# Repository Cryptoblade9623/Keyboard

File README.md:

# Keyboard
A custom keyboard with a white sakura theme and a rotary encoder.
I'm making this keyboard to have an upgrade from my dying membrane keyboard that also have a lot of the keycaps missing.
I also hope that this will give me some more experience in designing PCBs and 3D models.
Because it is quite a large keyboard that I will be 3D - printing in different parts, I found some metal rods to hold them together and provide some structural support.

Instructions

1.Solder all the diodes on to the PCB

2.Place all the Mill-Max hotswap sockets into their holes

3.Stick heat resistant tape over them in top rows to keep them in place while soldering

4.Solder all the hotswap sockets

5.Solder the pin headers

6.Solder the ESP32 onto the pin headers

7.Solder the Ec11x rotary encoder on to the PCB

8.Flash the ESP32 with the firmware

9.Screw in the PCB-mount stabilizers

10.Solder 4 wires onto the 4 pads of the USBC breakout board

11.Solder 2 small capacitors and 1 big capacitor in parallel on the 5V and GND wires

12.Place heat shrink tubing to cover the solder joints on the wires 

13.Superglue the USBC board into its slot inside the Left-Base part

14.Cut the all the metal rods to 50mm

15.Join the Base pieces together with the metal rods in their slots

16.Join all the Border pieces together again using the metal rods

17.Superglue all the mountain, sakura, grass and tree pieces onto the Scenery Border piece

18.Superglue both halves of the plate together

19.Press the heat set inserts into the Border piece with a soldering iron.

20.Slot the loose wires of the USBC board though the vertical slot hole in the PCB

21.Solder the USBC wires to the D+, D-, GND and RAW of the MCU

22.Stack the parts in the order: base, PCB, plate, border and screw them all together using the M3 bolts

23.Push in the switches

24.Push in all the keycaps onto their assigned switches

25.Snap both pieces of the knob together and push the combined knob onto the rotary encoder stem

And you're done!

| Name | Purpose | Price (USD) | Seller | Link |

| :--- | :--- | :--- | :--- |

| Screws & Standoffs | Spacing, mounting, and securing internal circuit boards | $2.23 | AliExpress |[Link](https://www.aliexpress.com/item/1005008314123679.html?spm=a2g0o.cart.0.0.16e738daMmvBdI&mp=1&pdp_npi=6%40dis%21USD%21USD%202.23%21USD%202.17%21%21USD%202.17%21%21%21%402103828617851600233073312e0d3f%2112000044581940836%21ct%21GB%21-1%21%211%210%21&pdp_ext_f=%7B%22cart2PdpParams%22%3A%7B%22pdpBusinessMode%22%3A%22retail%22%7D%7D)|

| 100nF Capacitors | Providing smooth current flow to the MCU | $2.27 | AliExpress |[Link](https://www.aliexpress.com/item/1005008314123679.html?spm=a2g0o.cart.0.0.16e738daMmvBdI&mp=1&pdp_npi=6%40dis%21USD%21USD%202.23%21USD%202.17%21%21USD%202.17%21%21%21%402103828617851600233073312e0d3f%2112000044581940836%21ct%21GB%21-1%21%211%210%21&pdp_ext_f=%7B%22cart2PdpParams%22%3A%7B%22pdpBusinessMode%22%3A%22retail%22%7D%7D)|

| PCB Stabilizers | Stabilizing large mechanical keyboard keys (e.g., Spacebar, Shift) | $10.58 | AliExpress |[Link](https://www.aliexpress.com/item/4001143514438.html?spm=a2g0o.cart.0.0.16e738daMmvBdI&mp=1&pdp_npi=6%40dis%21USD%21USD%2010.58%21USD%209.80%21%21USD%209.80%21%21%21%402103828617851600233073312e0d3f%2112000033301894110%21ct%21GB%21-1%21%211%210%21)|

| Keycaps | Providing durable, custom keycaps for mechanical keyboards | $7.74 | AliExpress |[Link](https://www.aliexpress.com/item/4001143514438.html?spm=a2g0o.cart.0.0.16e738daMmvBdI&mp=1&pdp_npi=6%40dis%21USD%21USD%2010.58%21USD%209.80%21%21USD%209.80%21%21%21%402103828617851600233073312e0d3f%2112000033301894110%21ct%21GB%21-1%21%211%210%21)|

| Mechanical Switches | Actuating keystrokes quietly and smoothly in hot-swap keyboards | $19.67 | AliExpress |[Link](https://www.aliexpress.com/item/1005012344423067.html?spm=a2g0o.cart.0.0.16e738daMmvBdI&mp=1&pdp_npi=6%40dis%21USD%21USD%2019.67%21USD%2018.50%21%21USD%2018.50%21%21%21%402103828617851600233073312e0d3f%2112000058131373053%21ct%21GB%21-1%21%211%210%21)|

| Rotary Encoder | Providing rotary control and navigation inputs | $2.75 | AliExpress |[Link](https://www.aliexpress.com/item/1005012344423067.html?spm=a2g0o.cart.0.0.16e738daMmvBdI&mp=1&pdp_npi=6%40dis%21USD%21USD%2019.67%21USD%2018.50%21%21USD%2018.50%21%21%21%402103828617851600233073312e0d3f%2112000058131373053%21ct%21GB%21-1%21%211%210%21)|

| Development Board | Processing core logic, Wi-Fi, and Bluetooth functions | $7.10 | AliExpress |[Link](https://www.aliexpress.com/item/1005007319706057.html?spm=a2g0o.cart.0.0.16e738daMmvBdI&mp=1&pdp_npi=6%40dis%21USD%21USD%207.10%21USD%206.69%21%21USD%206.69%21%21%21%402103828617851600233073312e0d3f%2112000058208354042%21ct%21GB%21-1%21%211%210%21&pdp_ext_f=%7B%22cart2PdpParams%22%3A%7B%22pdpBusinessMode%22%3A%22retail%22%7D%7D)|

| Hot-swap PCB Sockets | Enabling easy and simple mechanical switch replacement on a custom PCB | $14.77 | AliExpress |[Link](https://www.aliexpress.com/item/1005007319706057.html?spm=a2g0o.cart.0.0.16e738daMmvBdI&mp=1&pdp_npi=6%40dis%21USD%21USD%207.10%21USD%206.69%21%21USD%206.69%21%21%21%402103828617851600233073312e0d3f%2112000058208354042%21ct%21GB%21-1%21%211%210%21&pdp_ext_f=%7B%22cart2PdpParams%22%3A%7B%22pdpBusinessMode%22%3A%22retail%22%7D%7D)|

| USB Type-C Connector | Providing power delivery and data transfer interfaces | $1.25 | AliExpress |[Link](https://www.aliexpress.com/item/1005007319706057.html?spm=a2g0o.cart.0.0.16e738daMmvBdI&mp=1&pdp_npi=6%40dis%21USD%21USD%207.10%21USD%206.69%21%21USD%206.69%21%21%21%402103828617851600233073312e0d3f%2112000058208354042%21ct%21GB%21-1%21%211%210%21&pdp_ext_f=%7B%22cart2PdpParams%22%3A%7B%22pdpBusinessMode%22%3A%22retail%22%7D%7D)|

| Steel Rod Axles | Acting as structural pins or shafts for moving components | $4.58 | AliExpress |[Link](https://www.aliexpress.com/item/1005007319706057.html?spm=a2g0o.cart.0.0.16e738daMmvBdI&mp=1&pdp_npi=6%40dis%21USD%21USD%207.10%21USD%206.69%21%21USD%206.69%21%21%21%402103828617851600233073312e0d3f%2112000058208354042%21ct%21GB%21-1%21%211%210%21&pdp_ext_f=%7B%22cart2PdpParams%22%3A%7B%22pdpBusinessMode%22%3A%22retail%22%7D%7D)|

| Heatshrink | Cover soldered wire joints to prevent shorting | $0.85 | AliExpress |[Link](https://www.aliexpress.com/item/1005008538975205.html?spm=a2g0o.cart.0.0.d37038daXhhulS&mp=1&pdp_npi=6%40dis%21USD%21USD%201.00%21USD%200.85%21%21USD%200.85%21%21%21%400b884c0217861202998693843e0e67%2112000045622723973%21ct%21GB%21-1%21%211%210%21)|

| 10uF Capacitors | Providing smooth current flow to the MCU | $1.42 | AliExpress |[Link](https://www.aliexpress.com/item/1005008538975205.html?spm=a2g0o.cart.0.0.d37038daXhhulS&mp=1&pdp_npi=6%40dis%21USD%21USD%201.00%21USD%200.85%21%21USD%200.85%21%21%21%400b884c0217861202998693843e0e67%2112000045622723973%21ct%21GB%21-1%21%211%210%21)|

| Threaded Heat Set Inserts | Providing a thread to screw into | $2.30 | AliExpress |[Link](https://www.aliexpress.com/item/1005008666672949.html?spm=a2g0o.productlist.main.5.24602d7cRvAa4K&algo_pvid=6bd672a2-570e-4202-a909-3a52ef32261f&algo_exp_id=6bd672a2-570e-4202-a909-3a52ef32261f-4&pdp_ext_f=%7B%22order%22%3A%2214153%22%2C%22spu_best_type%22%3A%22price%22%2C%22eval%22%3A%221%22%2C%22fromPage%22%3A%22search%22%7D&pdp_npi=6%40dis%21USD%212.70%211.35%21%21%2118.04%218.99%21%402103828617872446138332557e0dfd%2112000046157335344%21sea%21UK%210%21ABX%211%210%21n_tag%3A-29910%3Bd%3A5213ade4%3Bm03_new_user%3A-29895%3BpisId%3A5000000210377206&curPageLogUid=Rat0uCX0YUx0&utparam-url=scene%3Asearch%7Cquery_from%3A%7Cx_object_id%3A1005008666672949%7C_p_origin_prod%3A)|

| Copper Braid | Remove excess solder | $3.16 | AliExpress |[Link](https://www.aliexpress.com/item/1005008666672949.html?spm=a2g0o.productlist.main.5.24602d7cRvAa4K&algo_pvid=6bd672a2-570e-4202-a909-3a52ef32261f&algo_exp_id=6bd672a2-570e-4202-a909-3a52ef32261f-4&pdp_ext_f=%7B%22order%22%3A%2214153%22%2C%22spu_best_type%22%3A%22price%22%2C%22eval%22%3A%221%22%2C%22fromPage%22%3A%22search%22%7D&pdp_npi=6%40dis%21USD%212.70%211.35%21%21%2118.04%218.99%21%402103828617872446138332557e0dfd%2112000046157335344%21sea%21UK%210%21ABX%211%210%21n_tag%3A-29910%3Bd%3A5213ade4%3Bm03_new_user%3A-29895%3BpisId%3A5000000210377206&curPageLogUid=Rat0uCX0YUx0&utparam-url=scene%3Asearch%7Cquery_from%3A%7Cx_object_id%3A1005008666672949%7C_p_origin_prod%3A|)

| Custom PCB | Connecting all the mechanical switches and rotary encoder to the MCU | $28.80 | JLCPCB |-|

| 3D Printed Case | Physical housing or structural frame for the custom keyboard | $3.00 | Printing Legion |-|

| Shipping and Taxes - $16.47

| Grand Total - $128.94|

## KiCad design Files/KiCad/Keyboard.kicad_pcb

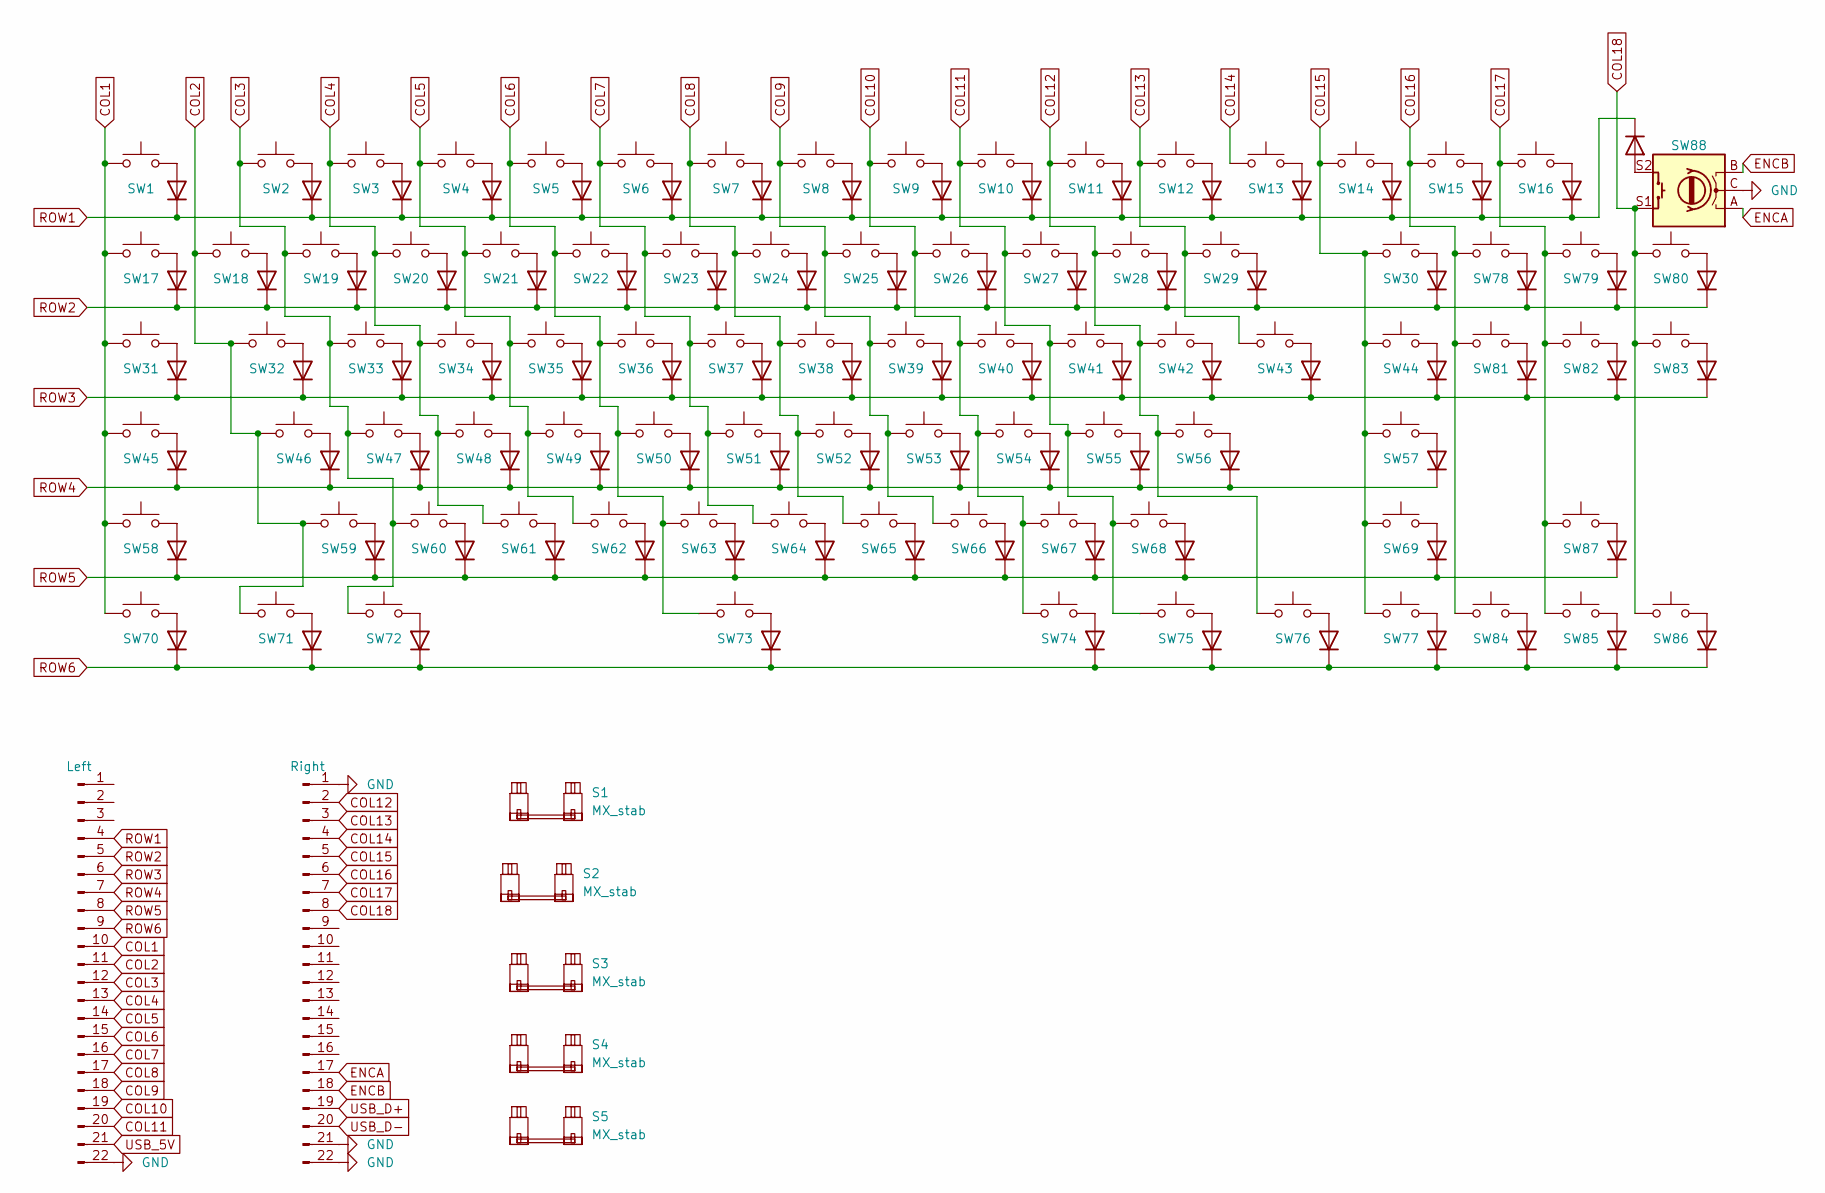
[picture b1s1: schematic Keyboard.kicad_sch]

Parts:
D1, D2, D3, D4, D5, D6, D7, D8, D9, D10, D11, D12, D13, D14, D15, D16, D17, D18, D19, D20, D21, D22, D23, D24, D25, D26, D27, D28, D29, D30, D31, D32, D33, D34, D35, D36, D37, D38, D39, D40, D41, D42, D43, D44, D45, D46, D47, D48, D49, D50, D51, D52, D53, D54, D55, D56, D57, D58, D59, D60, D61, D62, D63, D64, D65, D66, D67, D68, D69, D70, D71, D72, D73, D74, D75, D76, D77, D78, D79, D80, D81, D82, D83, D84, D85, D86, D87, D88: D; D_SOD-123
J1: Left; PinHeader_1x22_P2.54mm_Vertical
J2: Right; PinHeader_1x22_P2.54mm_Vertical
S1: MX_stab; STAB_MX_2u
S2, S3: MX_stab; STAB_MX_2.25u
S4: MX_stab; STAB_MX_2.75u
S5: MX_stab; STAB_MX_6.25u
SW1, SW2, SW3, SW4, SW5, SW6, SW7, SW8, SW9, SW10, SW11, SW12, SW13, SW14, SW15, SW16, SW17, SW18, SW19, SW20, SW21, SW22, SW23, SW24, SW25, SW26, SW27, SW28, SW29, SW30, SW32, SW33, SW34, SW35, SW36, SW37, SW38, SW39, SW40, SW41, SW42, SW43, SW46, SW47, SW48, SW49, SW50, SW51, SW52, SW53, SW54, SW55, SW56, SW57, SW58, SW59, SW60, SW61, SW62, SW63, SW64, SW65, SW66, SW67, SW68, SW69, SW73, SW78, SW79, SW80, SW81, SW82, SW83, SW84, SW85, SW86, SW87: SW_Push; SW_MX_HS_CPG151101S11_1u
SW31, SW44: SW_Push; SW_MX_HS_CPG151101S11_1.5u
SW45: SW_Push; SW_MX_HS_CPG151101S11_1.75u
SW70, SW71, SW72, SW74, SW75, SW76, SW77: SW_Push; SW_MX_HS_CPG151101S11_1.25u
SW88: RotaryEncoder_Switch; RotaryEncoder_Alps_EC11E-Switch_Vertical_H20mm

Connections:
COL1: J1.10, SW1.1, SW17.1, SW31.1, SW45.1, SW58.1, SW70.1
COL2: J1.11, SW18.1, SW32.1, SW46.1, SW59.1, SW71.1
COL3: J1.12, SW2.1, SW19.1, SW33.1, SW47.1, SW60.1, SW72.1
COL4: J1.13, SW3.1, SW20.1, SW34.1, SW48.1, SW61.1
COL5: J1.14, SW4.1, SW21.1, SW35.1, SW49.1, SW62.1
COL6: J1.15, SW5.1, SW22.1, SW36.1, SW50.1, SW63.1, SW73.1
COL7: J1.16, SW6.1, SW23.1, SW37.1, SW51.1, SW64.1
COL8: J1.17, SW7.1, SW24.1, SW38.1, SW52.1, SW65.1
COL9: J1.18, SW8.1, SW25.1, SW39.1, SW53.1, SW66.1
COL10: J1.19, SW9.1, SW26.1, SW40.1, SW54.1, SW67.1, SW74.1
COL11: J1.20, SW10.1, SW27.1, SW41.1, SW55.1, SW68.1, SW75.1
COL12: J2.2, SW11.1, SW28.1, SW42.1, SW56.1, SW76.1
COL13: J2.3, SW12.1, SW29.1, SW43.1
COL14: J2.4, SW13.1
COL15: J2.5, SW14.1, SW30.1, SW44.1, SW57.1, SW69.1, SW77.1
COL16: J2.6, SW15.1, SW78.1, SW81.1, SW84.1
COL17: J2.7, SW16.1, SW79.1, SW82.1, SW85.1, SW87.1
COL18: J2.8, SW80.1, SW83.1, SW86.1, SW88.S1
ENCA: J2.17, SW88.A
ENCB: J2.18, SW88.B
GND: J1.22, J2.1, J2.21, J2.22, SW88.C
unnamed: D1.2 (A), SW1.2
unnamed: D2.2 (A), SW2.2
unnamed: D3.2 (A), SW3.2
unnamed: D4.2 (A), SW4.2
unnamed: D5.2 (A), SW5.2
unnamed: D6.2 (A), SW6.2
unnamed: D7.2 (A), SW7.2
unnamed: D8.2 (A), SW8.2
unnamed: D9.2 (A), SW9.2
unnamed: D10.2 (A), SW10.2
unnamed: D11.2 (A), SW11.2
unnamed: D12.2 (A), SW12.2
unnamed: D13.2 (A), SW13.2
unnamed: D14.2 (A), SW14.2
unnamed: D15.2 (A), SW15.2
unnamed: D16.2 (A), SW16.2
unnamed: D17.2 (A), SW17.2
unnamed: D18.2 (A), SW18.2
unnamed: D19.2 (A), SW19.2
unnamed: D20.2 (A), SW20.2
unnamed: D21.2 (A), SW21.2
unnamed: D22.2 (A), SW22.2
unnamed: D23.2 (A), SW23.2
unnamed: D24.2 (A), SW24.2
unnamed: D25.2 (A), SW25.2
unnamed: D26.2 (A), SW26.2
unnamed: D27.2 (A), SW27.2
unnamed: D28.2 (A), SW28.2
unnamed: D29.2 (A), SW29.2
unnamed: D30.2 (A), SW30.2
unnamed: D31.2 (A), SW31.2
unnamed: D32.2 (A), SW32.2
unnamed: D33.2 (A), SW33.2
unnamed: D34.2 (A), SW34.2
unnamed: D35.2 (A), SW35.2
unnamed: D36.2 (A), SW36.2
unnamed: D37.2 (A), SW37.2
unnamed: D38.2 (A), SW38.2
unnamed: D39.2 (A), SW39.2
unnamed: D40.2 (A), SW40.2
unnamed: D41.2 (A), SW41.2
unnamed: D42.2 (A), SW42.2
unnamed: D43.2 (A), SW43.2
unnamed: D44.2 (A), SW44.2
unnamed: D45.2 (A), SW45.2
unnamed: D46.2 (A), SW46.2
unnamed: D47.2 (A), SW47.2
unnamed: D48.2 (A), SW48.2
unnamed: D49.2 (A), SW49.2
unnamed: D50.2 (A), SW50.2
unnamed: D51.2 (A), SW51.2
unnamed: D52.2 (A), SW52.2
unnamed: D53.2 (A), SW53.2
unnamed: D54.2 (A), SW54.2
unnamed: D55.2 (A), SW55.2
unnamed: D56.2 (A), SW56.2
unnamed: D57.2 (A), SW57.2
unnamed: D58.2 (A), SW58.2
unnamed: D59.2 (A), SW59.2
unnamed: D60.2 (A), SW60.2
unnamed: D61.2 (A), SW61.2
unnamed: D62.2 (A), SW62.2
unnamed: D63.2 (A), SW63.2
unnamed: D64.2 (A), SW64.2
unnamed: D65.2 (A), SW65.2
unnamed: D66.2 (A), SW66.2
unnamed: D67.2 (A), SW67.2
unnamed: D68.2 (A), SW68.2
unnamed: D69.2 (A), SW69.2
unnamed: D70.2 (A), SW70.2
unnamed: D71.2 (A), SW71.2
unnamed: D72.2 (A), SW72.2
unnamed: D73.2 (A), SW73.2
unnamed: D74.2 (A), SW74.2
unnamed: D75.2 (A), SW75.2
unnamed: D76.2 (A), SW76.2
unnamed: D77.2 (A), SW77.2
unnamed: D78.2 (A), SW78.2
unnamed: D79.2 (A), SW79.2
unnamed: D80.2 (A), SW80.2
unnamed: D81.2 (A), SW81.2
unnamed: D82.2 (A), SW82.2
unnamed: D83.2 (A), SW83.2
unnamed: D84.2 (A), SW84.2
unnamed: D85.2 (A), SW85.2
unnamed: D86.2 (A), SW86.2
unnamed: D87.2 (A), SW88.S2
unnamed: D88.2 (A), SW87.2
ROW1: D1.1 (K), D2.1 (K), D3.1 (K), D4.1 (K), D5.1 (K), D6.1 (K), D7.1 (K), D8.1 (K), D9.1 (K), D10.1 (K), D11.1 (K), D12.1 (K), D13.1 (K), D14.1 (K), D15.1 (K), D16.1 (K), D87.1 (K), J1.4
ROW2: D17.1 (K), D18.1 (K), D19.1 (K), D20.1 (K), D21.1 (K), D22.1 (K), D23.1 (K), D24.1 (K), D25.1 (K), D26.1 (K), D27.1 (K), D28.1 (K), D29.1 (K), D30.1 (K), D78.1 (K), D79.1 (K), D80.1 (K), J1.5
ROW3: D31.1 (K), D32.1 (K), D33.1 (K), D34.1 (K), D35.1 (K), D36.1 (K), D37.1 (K), D38.1 (K), D39.1 (K), D40.1 (K), D41.1 (K), D42.1 (K), D43.1 (K), D44.1 (K), D81.1 (K), D82.1 (K), D83.1 (K), J1.6
ROW4: D45.1 (K), D46.1 (K), D47.1 (K), D48.1 (K), D49.1 (K), D50.1 (K), D51.1 (K), D52.1 (K), D53.1 (K), D54.1 (K), D55.1 (K), D56.1 (K), D57.1 (K), J1.7
ROW5: D58.1 (K), D59.1 (K), D60.1 (K), D61.1 (K), D62.1 (K), D63.1 (K), D64.1 (K), D65.1 (K), D66.1 (K), D67.1 (K), D68.1 (K), D69.1 (K), D88.1 (K), J1.8
ROW6: D70.1 (K), D71.1 (K), D72.1 (K), D73.1 (K), D74.1 (K), D75.1 (K), D76.1 (K), D77.1 (K), D84.1 (K), D85.1 (K), D86.1 (K), J1.9
USB_5V: J1.21
USB_D+: J2.19
USB_D-: J2.20

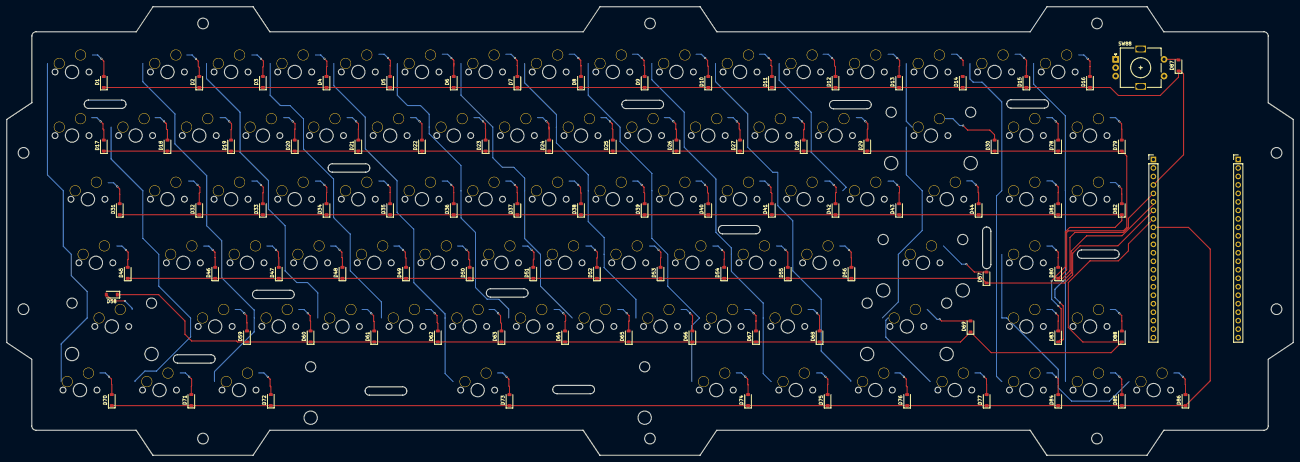
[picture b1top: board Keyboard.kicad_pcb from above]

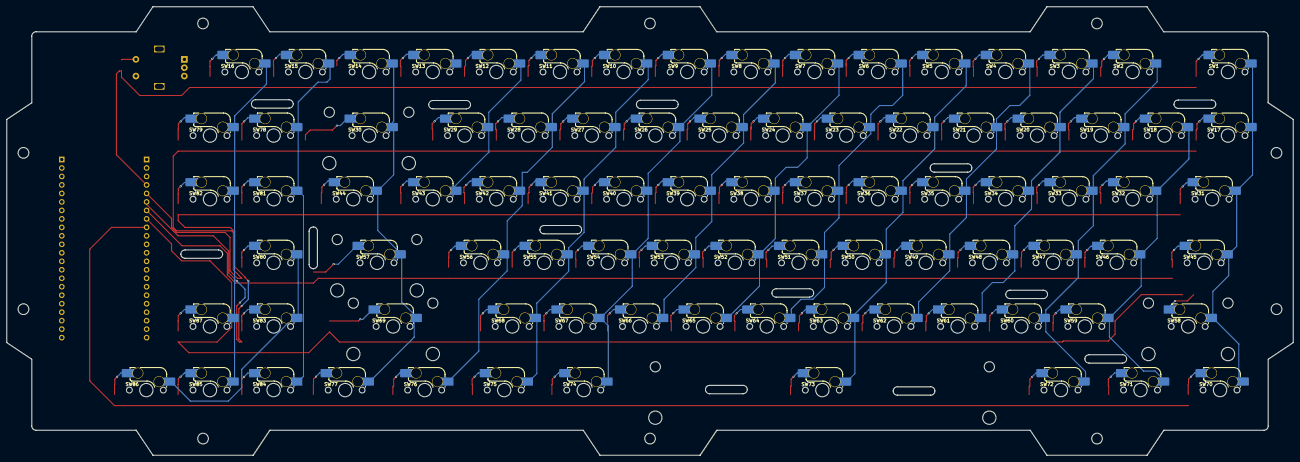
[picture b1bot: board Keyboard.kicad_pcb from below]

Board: 2 copper layers, 385.2 x 134.3 mm, 183 parts (87 on the bottom side), 115 nets.
